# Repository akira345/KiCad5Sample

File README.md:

* KiCad5勉強の為作成したサンプルです。  
トランジスタ1石のLEDスイッチング基板です。
* ベタGNDやスルーホール周り正しいのか自信がありませんｗ

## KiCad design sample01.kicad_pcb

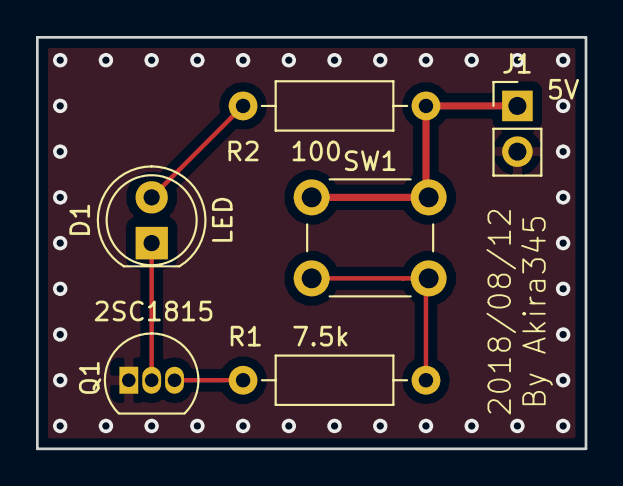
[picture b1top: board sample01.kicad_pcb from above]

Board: 2 copper layers, 30.5 x 22.9 mm, 6 parts (0 on the bottom side), 6 nets.

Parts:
D1: LED; LED_D5.0mm
J1: Power5V; PinHeader_1x02_P2.54mm_Vertical
Q1: 2SC1815; TO-92_Inline
R1: 7.5k; R_Axial_DIN0207_L6.3mm_D2.5mm_P10.16mm_Horizontal
R2: 100; R_Axial_DIN0207_L6.3mm_D2.5mm_P10.16mm_Horizontal
SW1: SW_Push; SW_PUSH_6mm

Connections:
+5V: J1.1, R2.1, SW1.1
GND: J1.2, Q1.1
unnamed: D1.1, Q1.2
unnamed: D1.2, R2.2
unnamed: Q1.3, R1.1
unnamed: R1.2, SW1.2

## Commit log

2018-08-03 My First Circuit
2018-08-03 add readme.md
2018-08-03 no message
2018-08-12 vcutを図形ポリゴンから図形ラインで書きなおす。
2018-08-12 謎の穴を削除！！
2018-08-12 ベタグラウンド張り直し。ベタを張りなおしたので不要な配線削除。
2018-08-12 シルク印字を入れる
2018-08-12 シルク印字位置調整
2018-08-12 ガーバーデータ再出力
2018-08-12 寸法線をシルクからDwgs.Userへ変更
